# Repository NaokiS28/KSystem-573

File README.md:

# KSystem-573
 Schematics and pinout information for the Konami System 573
 
 **Please note a lot of this data is not 100% complete and might be incorrect in places.** Also this repository needs to be generally organised better.
 
## Schematics
 Schematics are in KiCad format and are preliminary. Currently known issues:
 * The PSX portion is not mapped out. This is the same as the regular PS1 CPU, GPU and SPU schematics with the exception of more work and GPU RAM.
 * The CPLD is mostly but not fully mapped out.
 * The security cart needs verifying and labeling correctly.
 * In general the schematics need tidying up.
 * The Konami 056789 ASIC needs a symbol creating. It's a 6x 16-Bit input and 1x 8-bit output latch really, probably has some 74 series dies on the inside.
 * IO boards are somewhat documented but in varying stages of completeness.

## PCB Layout
 The mother PCB is not laid out. The intention with this project was not to make a new repro motherboard but to define the schematics and wiring. The outline *should* be correct but it is not 100%. If you feel like creating a PCB layout, submit a PR!

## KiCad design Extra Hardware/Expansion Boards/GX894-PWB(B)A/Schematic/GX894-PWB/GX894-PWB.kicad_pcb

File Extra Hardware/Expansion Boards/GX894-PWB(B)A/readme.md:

# Konami 573 Digital Audio I/O Board (GX894)

This is the IO board that is mostly used with Bemani rhythm games. It uses a SPARTAN FPGA, Xilinx XC9536 CPLD and MAS3507D MP3 audio decoder IC withh a bunch of RAM, opto-isolators and trasceivers thrown in for good measure. The board is practically useless without an FPGA binary blob uploaded to it as nothing is accessible otherwise. This is uploaded by the game at the game's boot (and will show "Digital I/O init failure" if it can't.).

There's a dual RS232 port on the board but it seeminly went unused. There's also I2S audio output so it would be possible to capture the digital audio from the cab (and from the mainboard too) and convert to SPDIF or TOSLINK.

FWIW, the FPGA Blob that Konami uses is stored in 128k of SRAM and has a decryption engine built in that feeds data to the MAS chip, so you would need to encrypt any audio to be played back to use Konami's blob. Otherwise you could create a alternate blob that didn't require this and just use MP3 data stored in the 12 megabytes (!) of EDO RAM on the board.

There is Konami's multidrop networking bus and interface present on the board but more needs to be understood about this before it can be documented fully.

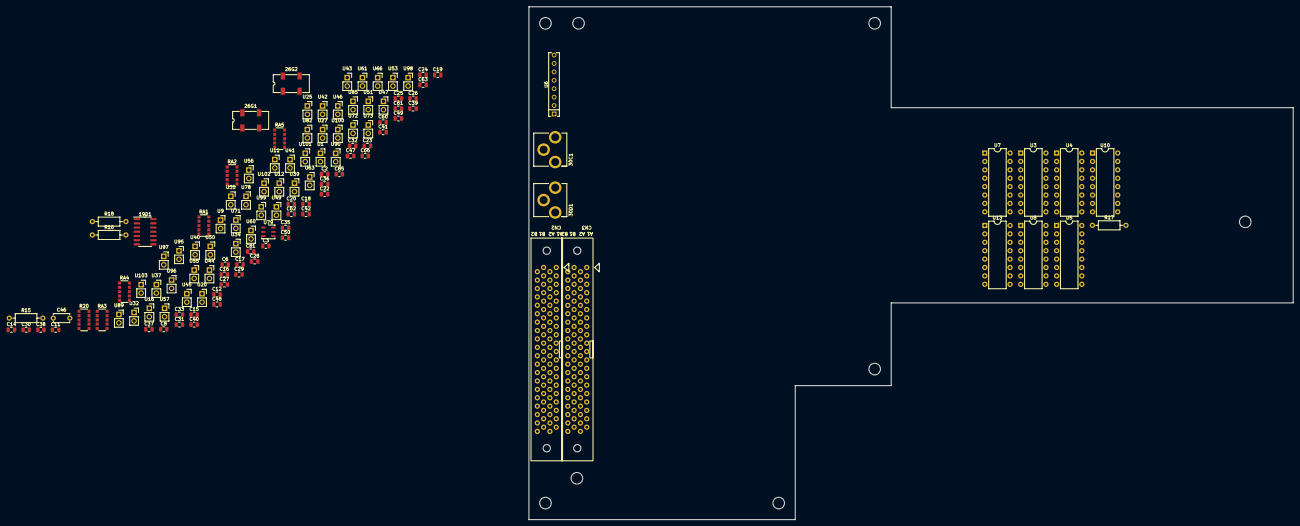
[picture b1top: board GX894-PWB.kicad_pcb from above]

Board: 2 copper layers, 231.0 x 155.0 mm, 128 parts (0 on the bottom side), 124 nets, no tracks yet.

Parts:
19D1: 74HC14; SOIC-14_3.9x8.7mm_P1.27mm
26G1: 29.45MHz; Oscillator_SMD_SeikoEpson_SG8002JC-4Pin_10.5x5.0mm
26G2: 19.6608 MHz; Oscillator_SMD_SeikoEpson_SG8002JC-4Pin_10.5x5.0mm
30C1, 30D1: JPJ1018; RCA_Mounting
C2, C3, C6, C8, C11, C12, C28, C29: 0.1µf; C_0805_2012Metric
C14, C15, C16, C17, C18, C19, C22, C23, C24, C25, C26, C27, C30, C31, C32, C33, C35, C36, C37, C38, C39, C40, C41, C42, C47, C48, C49, C50, C60, C61, C62, C63: 10nf; C_0805_2012Metric
C20, C66, C81, C85: 1uf; C_0805_2012Metric
C46: 0.01MC1K; C_Disc_D4.7mm_W2.5mm_P5.00mm
CN2, CN3: 573_EXP; JAE-TX15-80P
H1, H2, H3, H4, H5, H6, H7, H8: MountingHole; MountingHole_3.5mm
R15, R18: 100; R_Axial_DIN0207_L6.3mm_D2.5mm_P10.16mm_Horizontal
R16, R17: 5.6k; R_Axial_DIN0207_L6.3mm_D2.5mm_P10.16mm_Horizontal
R20: 470Ω; R_Array_Convex_5x1206
RA1: 4.7Ω; R_Array_Convex_5x1206
RA2, RA3, RA4: 470Ω; R_Array_Convex_5x1206
RA5: 2.2k; R_Array_Convex_5x1206
U1, U9, U11, U12, U16, U20, U25, U27, U32, U34, U35, U37, U39, U40, U41, U42, U43, U44, U45, U46, U47, U49, U50, U51, U53, U55, U56, U57, U60, U61, U63, U66, U71, U72, U73, U78, U82, U85, U89, U90, U95, U96, U97, U98, U99, U100, U101, U102, U103: ZBF253D; PinSocket_1x02_P2.54mm_Vertical
U3, U4, U5, U7, U8, U10, U13: PC847; DIP-16_W7.62mm
U6: HYC2485S; SIP-8_19x3mm_P2.54mm
U79: DS2401P; TSOC-6_3.76x3.94mm_P1.27mm

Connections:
573-A0: CN2.a24 (A0), CN3.a24 (A0)
573-A1: CN2.b24 (A1), CN3.b24 (A1)
573-A2: CN2.a23 (A2), CN3.a23 (A2)
573-A3: CN2.b23 (A3), CN3.b23 (A3)
573-A4: CN2.a22 (A4), CN3.a22 (A4)
573-A5: CN2.b22 (A5), CN3.b22 (A5)
573-A6: CN2.a21 (A6), CN3.a21 (A6)
573-A7: CN2.b21 (A7), CN3.b21 (A7)
573-A12: CN2.a20 (A12), CN3.a20 (A12)
573-A13: CN2.b20 (A13), CN3.b20 (A13)
573-A14: CN2.a19 (A14), CN3.a19 (A14)
573-A15: CN2.b19 (A15), CN3.b19 (A15)
573-A20: CN2.a18 (A20), CN3.a18 (A20)
573-A21: CN2.b18 (A21), CN3.b18 (A21)
573-A22: CN2.a17 (A22), CN3.a17 (A22)
573-A23: CN2.b17 (A23), CN3.b17 (A23)
573-D0: CN2.a32 (D0), CN3.a32 (D0)
573-D1: CN2.b32 (D1), CN3.b32 (D1)
573-D2: CN2.a31 (D2), CN3.a31 (D2)
573-D3: CN2.b31 (D3), CN3.b31 (D3)
573-D4: CN2.a30 (D4), CN3.a30 (D4)
573-D5: CN2.b30 (D5), CN3.b30 (D5)
573-D6: CN2.a29 (D6), CN3.a29 (D6)
573-D7: CN2.b29 (D7), CN3.b29 (D7)
573-D8: CN2.a28 (D8), CN3.a28 (D8)
573-D9: CN2.b28 (D9), CN3.b28 (D9)
573-D10: CN2.a27 (D10), CN3.a27 (D10)
573-D11: CN2.b27 (D11), CN3.b27 (D11)
573-D12: CN2.a26 (D12), CN3.a26 (D12)
573-D13: CN2.b26 (D13), CN3.b26 (D13)
573-D14: CN2.a25 (D14), CN3.a25 (D14)
573-D15: CN2.b25 (D15), CN3.b25 (D15)
+3V3: 26G1.1 (OE), 26G1.4 (Vcc), 26G2.1 (OE), 26G2.4 (Vcc), CN2.a36 (+3V3), CN2.a37 (+3V3), CN2.a38 (+3V3), CN2.a39 (+3V3), CN2.a40 (+3V3), CN2.b36 (+3V3), CN2.b37 (+3V3), CN2.b38 (+3V3), CN2.b39 (+3V3), CN2.b40 (+3V3), CN3.a36 (+3V3), CN3.a37 (+3V3), CN3.a38 (+3V3), CN3.a39 (+3V3), CN3.a40 (+3V3), CN3.b36 (+3V3), CN3.b37 (+3V3), CN3.b38 (+3V3), CN3.b39 (+3V3), CN3.b40 (+3V3)
+5V: 19D1.14 (VCC), C3.1, C20.1, C28.1, C66.1, C81.1, C85.1, CN2.a1 (+5V), CN2.a2 (+5V), CN2.a3 (+5V), CN2.a4 (+5V), CN2.a5 (+5V), CN2.b1 (+5V), CN2.b2 (+5V), CN2.b3 (+5V), CN2.b4 (+5V), CN2.b5 (+5V), CN3.a1 (+5V), CN3.a2 (+5V), CN3.a3 (+5V), CN3.a4 (+5V), CN3.a5 (+5V), CN3.b1 (+5V), CN3.b2 (+5V), CN3.b3 (+5V), CN3.b4 (+5V), CN3.b5 (+5V), R20.5 (common), R20.10 (common), RA1.5 (common), RA1.10 (common), RA2.5 (common), RA2.10 (common), RA3.5 (common), RA3.10 (common), RA4.5 (common), RA4.10 (common), U6.2 (VCC), U46.1
DREQ5: CN2.a14 (DREQ5), CN3.a14 (DREQ5)
DREQ5-2: CN2.b12 (DREQ5), CN3.b12 (DREQ5)
EXP-15: CN2.b15 (N/C), CN3.b15 (N/C)
GND: 19D1.1, 19D1.3, 19D1.7 (GND), 26G1.2 (GND), 26G2.2 (GND), C6.1, C11.1, C20.2, C30.2, C31.2, C32.2, C33.2, C46.2, C66.2, C81.2, C85.2, CN2.a8 (GND), CN2.a9 (GND), CN2.a11 (GND), CN2.a13 (GND), CN2.a33 (GND), CN2.a34 (GND), CN2.a35 (GND), CN2.b7 (GND), CN2.b9 (GND), CN2.b11 (GND), CN2.b13 (GND), CN2.b33 (GND), CN2.b34 (GND), CN2.b35 (GND), CN3.a8 (GND), CN3.a9 (GND), CN3.a11 (GND), CN3.a13 (GND), CN3.a33 (GND), CN3.a34 (GND), CN3.a35 (GND), CN3.b7 (GND), CN3.b9 (GND), CN3.b11 (GND), CN3.b13 (GND), CN3.b33 (GND), CN3.b34 (GND), CN3.b35 (GND), R16.1, RA5.5 (common), RA5.10 (common), U6.6 (GND), U12.1, U41.1, U47.1
IRQ10: CN2.a16 (IRQ10), CN3.a16 (IRQ10)
IRQ10-2: CN2.b16 (IRQ10), CN3.b16 (IRQ10)
unnamed: 19D1.5, C31.1
unnamed: 19D1.9, C33.1
unnamed: 19D1.11, C32.1
unnamed: 19D1.13, C30.1
unnamed: 30C1.1, 30D1.1, U6.5 (PH-A)
unnamed: 30C1.2 (Switch), R15.2
unnamed: 30C1.3 (Sheild), 30D1.3 (Sheild), C46.1, R15.1, R17.2, R18.2, U6.4 (PH-B)
unnamed: 30D1.2 (Switch), R18.1
unnamed: C14.1, U13.16, U25.1
unnamed: C14.2, C15.2, C16.2, C17.2, U13.9, U13.11, U13.13, U13.15, U60.1
unnamed: C15.1, U13.14, U102.1
unnamed: C16.1, U13.12, U101.1
unnamed: C17.1, U13.10, U100.1
unnamed: C18.1, U3.16, U99.1
unnamed: C18.2, C19.2, C38.2, C40.2, U3.9, U3.11, U3.13, U3.15, U50.1
unnamed: C19.1, U3.14, U98.1
unnamed: C22.1, U4.16, U95.1
unnamed: C22.2, C23.2, C24.2, C25.2, U4.9, U4.11, U4.13, U4.15, U35.1
unnamed: C23.1, U4.14, U44.1
unnamed: C24.1, U4.12, U90.1
unnamed: C25.1, U4.10, U82.1
unnamed: C26.1, U5.16, U89.1
unnamed: C26.2, C27.2, C35.2, C36.2, U5.9, U5.11, U5.13, U5.15, U45.1
unnamed: C27.1, U5.14, U71.1
unnamed: C35.1, U5.12, U34.1
unnamed: C36.1, U5.10, U40.1
unnamed: C37.1, U10.16, U73.1
unnamed: C37.2, C61.2, C62.2, C63.2, U10.9, U10.11, U10.13, U10.15, U72.1
unnamed: C38.1, U3.10, U96.1
unnamed: C39.1, U1.1, U8.10
unnamed: C39.2, C41.2, C42.2, C47.2, U8.9, U8.11, U8.13, U8.15, U63.1
unnamed: C40.1, U3.12, U97.1
unnamed: C41.1, U8.12, U9.1
unnamed: C42.1, U8.14, U16.1
unnamed: C47.1, U8.16, U27.1
unnamed: C48.1, U7.10, U39.1
unnamed: C48.2, C49.2, C50.2, C60.2, U7.9, U7.11, U7.13, U7.15, U37.1
unnamed: C49.1, U7.14, U53.1
unnamed: C50.1, U7.12, U43.1
unnamed: C60.1, U7.16, U56.1
unnamed: C61.1, U10.10, U103.1
unnamed: C62.1, U10.12, U51.1
unnamed: C63.1, U10.14, U61.1
unnamed: R16.2, R17.1
unnamed: R20.1 (R1), U7.1
unnamed: R20.2 (R2), U7.3
unnamed: R20.3 (R3), U7.5
unnamed: R20.4 (R4), U7.7
unnamed: R20.6 (R5), U8.7
unnamed: R20.7 (R6), U8.5
unnamed: R20.8 (R7), U8.3
unnamed: R20.9 (R8), U8.1
unnamed: RA1.1 (R1), RA5.1 (R1), U20.1
unnamed: RA1.4 (R4), RA5.4 (R4), U57.1
unnamed: RA1.3 (R3), RA5.3 (R3), U49.1
unnamed: RA1.2 (R2), RA5.2 (R2), U32.1
unnamed: RA2.1 (R1), U10.1
unnamed: RA2.2 (R2), U10.3
unnamed: RA2.3 (R3), U10.5
unnamed: RA2.4 (R4), U10.7
unnamed: RA2.6 (R5), U13.7
unnamed: RA2.7 (R6), U13.5
unnamed: RA2.8 (R7), U13.3
unnamed: RA2.9 (R8), U13.1
unnamed: RA3.1 (R1), U3.1
unnamed: RA3.2 (R2), U3.3
unnamed: RA3.3 (R3), U3.5
unnamed: RA3.4 (R4), U3.7
unnamed: RA3.6 (R5), U4.7
unnamed: RA3.7 (R6), U4.5
unnamed: RA3.8 (R7), U4.3
unnamed: RA3.9 (R8), U4.1
unnamed: RA4.1 (R1), U5.1
unnamed: RA4.2 (R2), U5.3
unnamed: RA4.3 (R3), U5.5
unnamed: RA4.4 (R4), U5.7
~EXP1-2: CN2.b14 (~EXP1), CN3.b14 (~EXP1)
~EXP1: CN2.a12 (~EXP1), CN3.a12 (~EXP1)
~EXP2: CN2.a15 (~EXP2), CN3.a15 (~EXP2)
~READ: CN2.a6 (~READ), CN3.a6 (~READ)
~RESET2: CN2.b10 (~RESET), CN3.b10 (~RESET)
~RESET: CN2.a10 (~RESET), CN3.a10 (~RESET)
~WR1: CN2.b6 (~WR1), CN3.b6 (~WR1)
~WR2: CN2.a7 (~WR2), CN3.a7 (~WR2)

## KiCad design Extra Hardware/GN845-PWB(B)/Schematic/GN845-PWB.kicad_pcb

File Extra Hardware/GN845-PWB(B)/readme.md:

# GN845-PWB(B) - Stage IO
This PCB is also known as the Stage IO board. It lives in either the top right or top left corner of the stage pads in Dance Dance Revolution/Dancing Stage and serves as a multiplexor and driver board for the stage neons. It's only used in DDR doubles cabs, DDR Solo does not use a multiplexor as it only uses two sensors per pad (vs DDR doubles' 4) and directly connects all sensors to the JAMMA connector. The JAMMA stick UDLR pins are connected to the Stage IO board, with U and R serving as inputs for the multiplexor data as well during boot and diagnostics.

Curiosly, the Stage IO is only ever populated for 4 arrows but an entire 5th section is on the PCB and routed out, so maybe DDR might have been a 5 panel game? This was before Pump-It-Up was released so it's interesting that perhaps the center panel might have originally been an input.

Power wise, the board receives a 12V input which is then connected to a 7805 to get local 5V regulated power.

## Function
The Stage IO is not exactly required in the sense that normal gameplay in DDR does not use nor care for the multiplexing of the Stage IO, it uses the direct JAMMA stick inputs for the arrows. That said the game *does* clock the Stage IO's serial bus during gameplay but it's not fully known why as grounding one of the pins (todo: which?) will enable the pad output anyway.

### Arrow Sections
Each arrow has it's own NPN darlington pair transistor, 74HC14 inverter and passives. The transistor is used for the neon drivers that light up the arrow panel. All sensors and the NPN transistor go through the logic inverter and then into the CPLD.

### CPLD
The CPLD has pullups on it's inputs after line filters (10nf LCL filters) that go through a resistor network. The inputs are also protected by a zener diode arrays to ground and to power. The outputs are protected by opto-isolators, the same PC817 chips that Konami used everywhere else.

The CPLD itself is not yet fully understood. It's known that all Stage IOs use a synchronous serial bus over 4 wires, two of which are inputs and driven by the System 573's opto-isolated outputs on the analogue or digital IO board. The other two lines share the U and R pins with the JAMMA connector. 

The serial protocol is **ludicrously slow**, it takes about 200ms(!) to transmit a complete message. The bus is full-duplex, like SPI, the 573 will receive data as it is being sent. The first packet is a mirror of what the 573 sends, the latter half has all of the sensor data (4x4 so 16 sensors) and the 573 can optionally disable individual sensors from use, probably to avoid a stuck input but this isn't used in gameplay.

The protocol will be documented here when it is more fully understood.

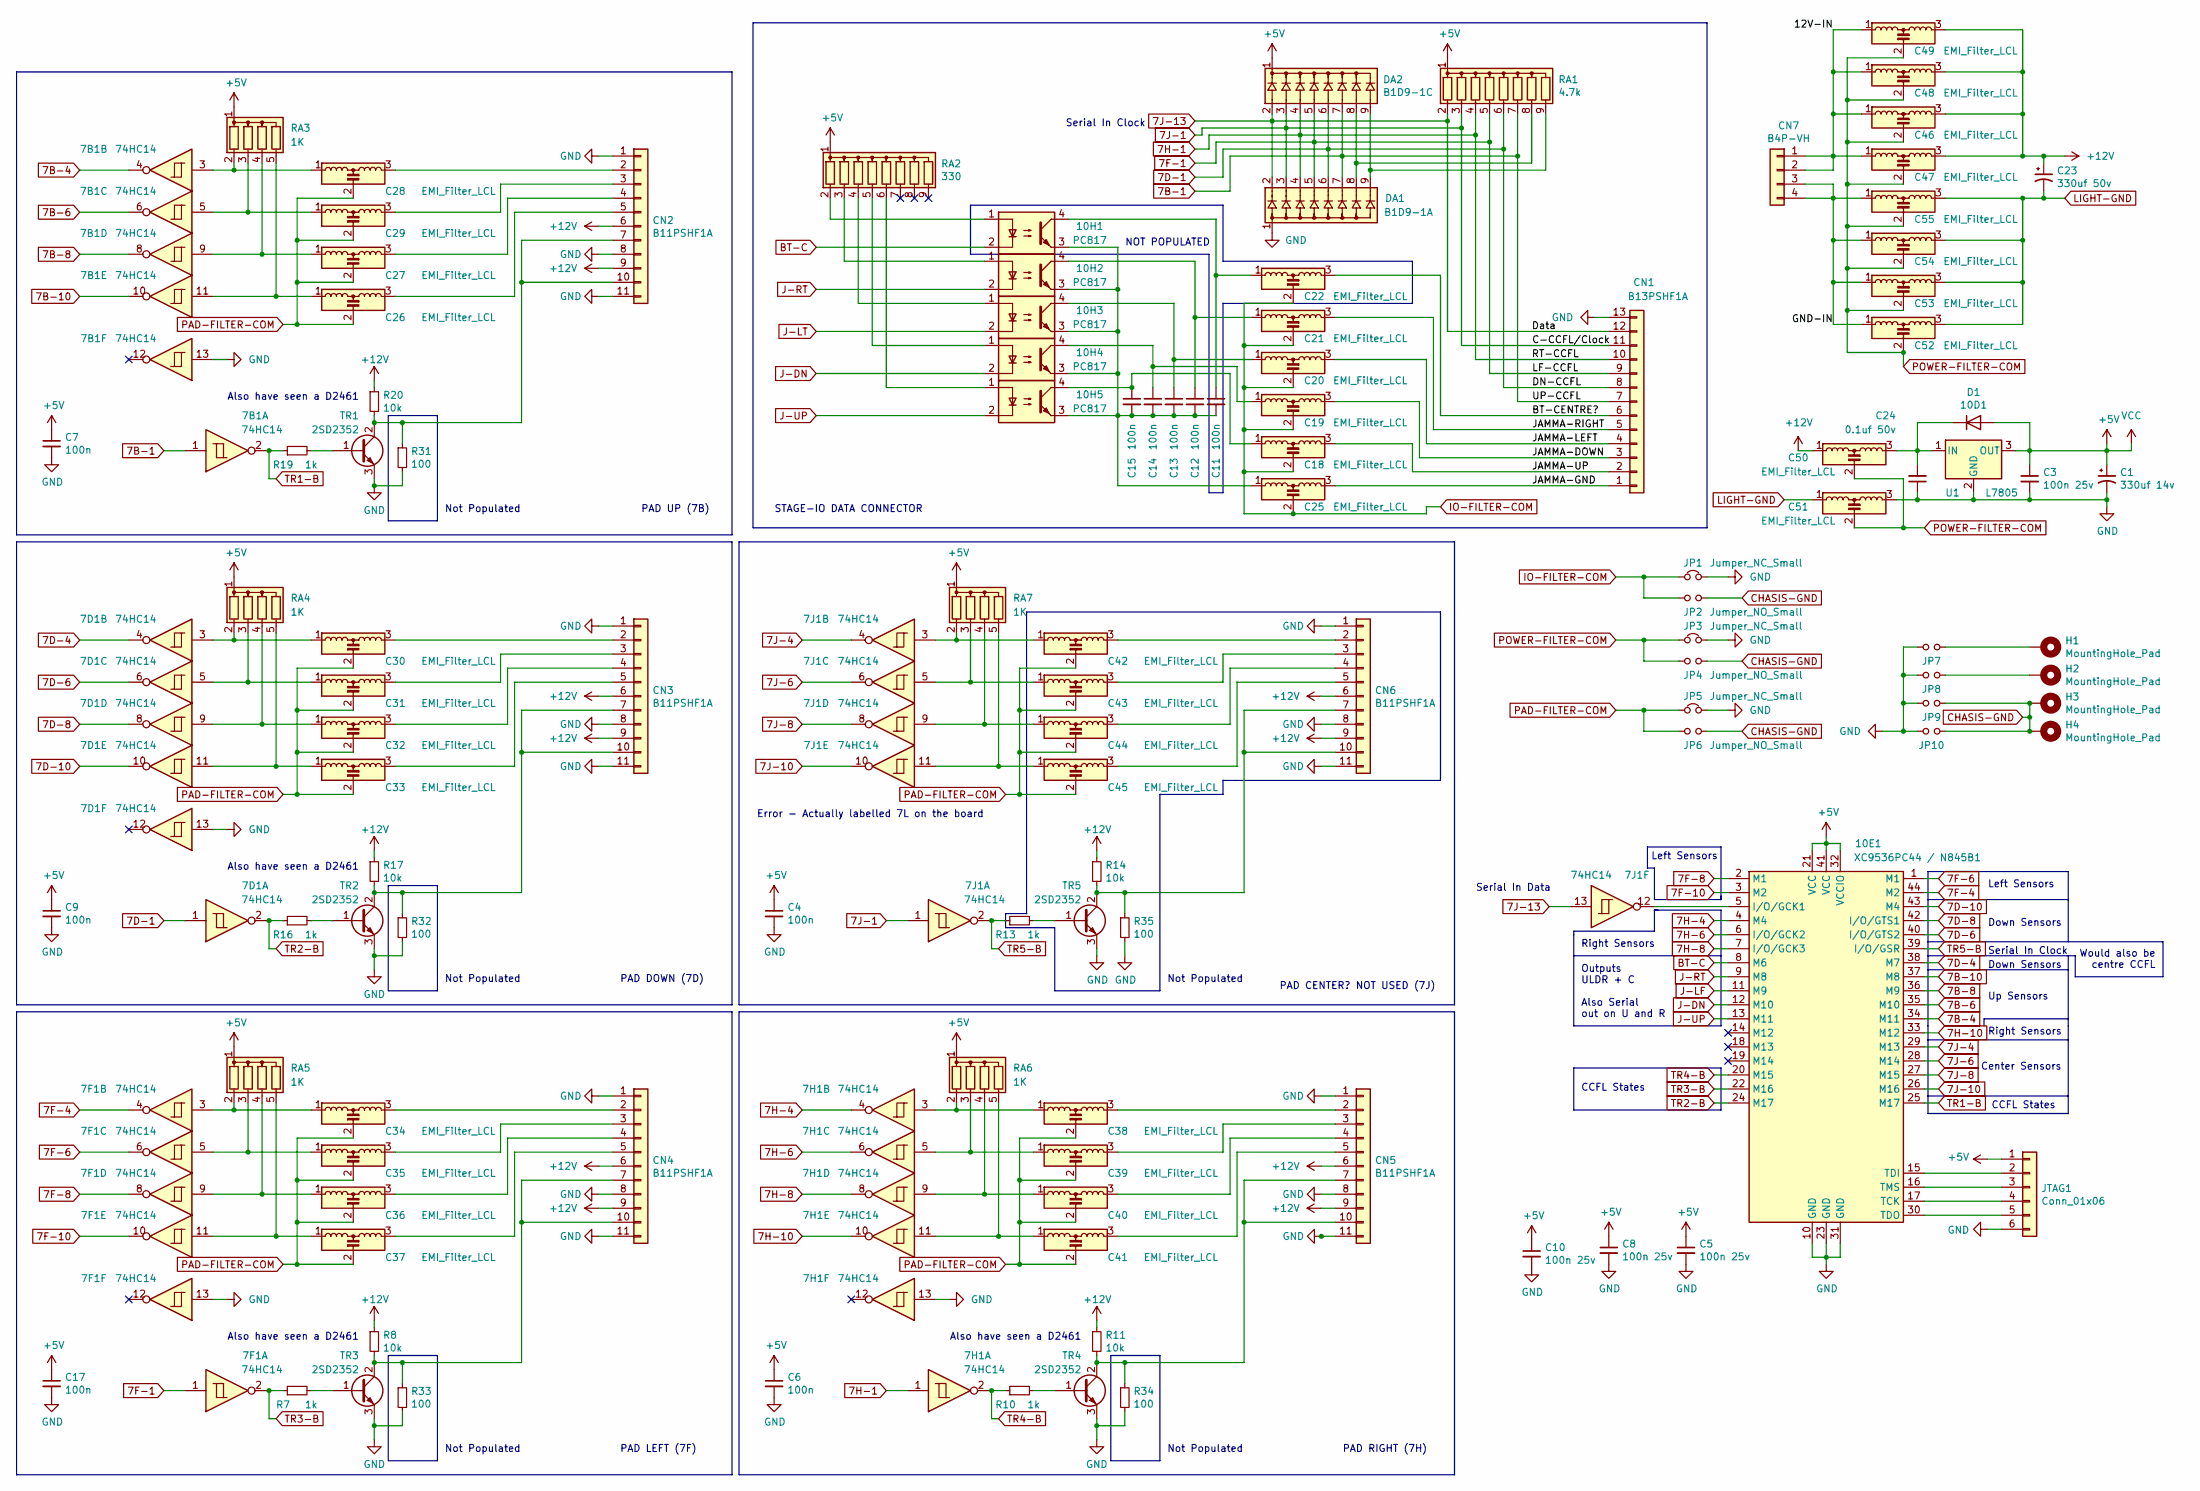
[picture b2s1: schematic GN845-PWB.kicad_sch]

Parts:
7B1, 7D1, 7F1, 7H1, 7J1: 74HC14; DIP-14_W7.62mm
10E1: XC9536PC44 / N845B1; PLCC-44
10H1, 10H2, 10H3, 10H4, 10H5: PC817; DIP-4_W7.62mm
C1: 330uf 14v; CP_Radial_D8.0mm_P3.50mm
C3, C5, C8, C10: 100n 25v; C_Axial_L3.8mm_D2.6mm_P10.00mm_Horizontal
C4, C6, C7, C9, C11, C12, C13, C14, C15, C17: 100n; C_Axial_L3.8mm_D2.6mm_P10.00mm_Horizontal
C18, C19, C20, C21, C22, C25, C26, C27, C28, C29, C30, C31, C32, C33, C34, C35, C36, C37, C38, C39, C40, C41, C42, C43, C44, C45, C46, C47, C48, C49, C50, C51, C52, C53, C54, C55: EMI_Filter_LCL; PinSocket_1x03_P2.54mm_Vertical
C23: 330uf 50v; CP_Radial_D8.0mm_P3.50mm
C24: 0.1uf 50v; C_Disc_D4.7mm_W2.5mm_P5.00mm
CN1: B13PSHF1A; JST_NH_B13P_SHD
CN2, CN3, CN4, CN5, CN6: B11PSHF1A; JST_NH_B11P_SHD
CN7: B4P-VH; JST_VH_B4P-VH-B_1x04_P3.96mm_Vertical
D1: 10D1; D_DO-41_SOD81_P10.16mm_Horizontal
DA1: B1D9-1A; SIP9_Housing
DA2: B1D9-1C; SIP9_Housing
H1, H2, H3, H4: MountingHole_Pad; MountingHole_3.2mm_M3_DIN965_Pad
JP1, JP3, JP5: Jumper_NC_Small; C_Rect_L7.0mm_W2.0mm_P5.00mm
JP2, JP4, JP6, JP7, JP8, JP9, JP10: Jumper_NO_Small; C_Rect_L7.0mm_W2.0mm_P5.00mm
JTAG1: Conn_01x06
R7, R10, R13, R16, R19: 1k; R_Axial_DIN0204_L3.6mm_D1.6mm_P5.08mm_Vertical
R8, R11, R14, R17, R20: 10k; R_Axial_DIN0204_L3.6mm_D1.6mm_P5.08mm_Vertical
R31, R32, R33, R34, R35: 100; R_Axial_DIN0204_L3.6mm_D1.6mm_P5.08mm_Vertical
RA1: 4.7k; R_Array_SIP9
RA2: 330; R_Array_SIP9
RA3, RA4, RA5, RA6, RA7: 1K; R_Array_SIP5
TR1, TR2, TR3, TR4, TR5: 2SD2352; TO-220-3_Horizontal_TabDown
U1: L7805; TO-220-3_Horizontal_TabDown

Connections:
7B-1: 7B1.1, CN1.7, DA1.7 (R6), DA2.7 (R6), RA1.7 (R6)
7B-4: 7B1.4, 10E1.34 (M11)
7B-6: 7B1.6, 10E1.35 (M10)
7B-8: 7B1.8, 10E1.36 (M9)
7B-10: 7B1.10, 10E1.37 (M8)
7D-1: 7D1.1, CN1.8, DA1.6 (R5), DA2.6 (R5), RA1.6 (R5)
7D-4: 7D1.4, 10E1.38 (M7)
7D-6: 7D1.6, 10E1.40 (I/O/GTS2)
7D-8: 7D1.8, 10E1.42 (I/O/GTS1)
7D-10: 7D1.10, 10E1.43 (M4)
7F-1: 7F1.1, CN1.9, DA1.5 (R4), DA2.5 (R4), RA1.5 (R4)
7F-4: 7F1.4, 10E1.44 (M2)
7F-6: 7F1.6, 10E1.1 (M1)
7F-8: 7F1.8, 10E1.2 (M1)
7F-10: 7F1.10, 10E1.3 (M2)
7H-1: 7H1.1, CN1.10, DA1.4 (R3), DA2.4 (R3), RA1.4 (R3)
7H-4: 7H1.4, 10E1.4 (M4)
7H-6: 7H1.6, 10E1.6 (I/O/GCK2)
7H-8: 7H1.8, 10E1.7 (I/O/GCK3)
7H-10: 7H1.10, 10E1.33 (M12)
7J-1: 7J1.1, CN1.11, DA1.3 (R2), DA2.3 (R2), RA1.3 (R2)
7J-4: 7J1.4, 10E1.29 (M13)
7J-6: 7J1.6, 10E1.28 (M14)
7J-8: 7J1.8, 10E1.27 (M15)
7J-10: 7J1.10, 10E1.26 (M16)
7J-13: 7J1.13, CN1.12, DA1.2 (R1), DA2.2 (R1), RA1.2 (R1)
+5V: 10E1.21 (VCC), 10E1.32 (VCCIO), 10E1.41 (VCC), C1.1, C3.1, C4.1, C5.1, C6.1, C7.1, C8.1, C9.1, C10.1, C17.1, D1.2 (A), DA2.1 (common), JTAG1.1, RA1.1 (common), RA2.1 (common), RA3.1 (common), RA4.1 (common), RA5.1 (common), RA6.1 (common), RA7.1 (common), U1.3 (OUT)
+12V: C23.1, C46.3, C47.3, C48.3, C49.3, C50.1, CN2.6, CN2.9, CN3.6, CN3.9, CN4.6, CN4.9, CN5.6, CN5.9, CN6.6, CN6.9, R8.1, R11.1, R14.1, R17.1, R20.1
/12V-IN: C46.1, C47.1, C48.1, C49.1, CN7.1, CN7.2
/BT-CENTRE?: C22.3, CN1.6
/GND-IN: C52.1, C53.1, C54.1, C55.1, CN7.3, CN7.4
/JAMMA-DOWN: C19.3, CN1.3
/JAMMA-GND: C25.3, CN1.1
/JAMMA-LEFT: C20.3, CN1.4
/JAMMA-RIGHT: C21.3, CN1.5
/JAMMA-UP: C18.3, CN1.2
BT-C: 10E1.8 (M6), 10H1.2
CHASIS-GND: H3.1, H4.1, JP2.2, JP4.2, JP6.2, JP9.2, JP10.2
GND: 7B1.13, 7D1.13, 7F1.13, 7H1.13, 10E1.10 (GND), 10E1.23 (GND), 10E1.31 (GND), C1.2, C3.2, C4.2, C5.2, C6.2, C7.2, C8.2, C9.2, C10.2, C17.2, C24.1, C51.3, CN1.13, CN2.1, CN2.8, CN2.11, CN3.1, CN3.8, CN3.11, CN4.1, CN4.8, CN4.11, CN5.1, CN5.8, CN5.11, CN6.1, CN6.8, CN6.11, DA1.1 (common), JP1.2, JP3.2, JP5.2, JP7.1, JP8.1, JP9.1, JP10.1, JTAG1.6, R31.2, R32.2, R33.2, R34.2, R35.2, TR1.3 (E), TR2.3 (E), TR3.3 (E), TR4.3 (E), TR5.3 (E), U1.2 (GND)
IO-FILTER-COM: C18.2, C19.2, C20.2, C21.2, C22.2, C25.2, JP1.1, JP2.1
J-DN: 10E1.12 (M10), 10H4.2
J-LF: 10E1.11 (M9)
J-LT: 10H3.2
J-RT: 10E1.9 (M8), 10H2.2
J-UP: 10E1.13 (M11), 10H5.2
LIGHT-GND: C23.2, C51.1, C52.3, C53.3, C54.3, C55.3
unnamed: 7B1.3, C28.1, RA3.2 (R1)
unnamed: 7B1.5, C29.1, RA3.3 (R2)
unnamed: 7B1.9, C27.1, RA3.4 (R3)
unnamed: 7B1.11, C26.1, RA3.5 (R4)
unnamed: 7D1.3, C30.1, RA4.2 (R1)
unnamed: 7D1.5, C31.1, RA4.3 (R2)
unnamed: 7D1.9, C32.1, RA4.4 (R3)
unnamed: 7D1.11, C33.1, RA4.5 (R4)
unnamed: 7F1.3, C34.1, RA5.2 (R1)
unnamed: 7F1.5, C35.1, RA5.3 (R2)
unnamed: 7F1.9, C36.1, RA5.4 (R3)
unnamed: 7F1.11, C37.1, RA5.5 (R4)
unnamed: 7H1.3, C38.1, RA6.2 (R1)
unnamed: 7H1.5, C39.1, RA6.3 (R2)
unnamed: 7H1.9, C40.1, RA6.4 (R3)
unnamed: 7H1.11, C41.1, RA6.5 (R4)
unnamed: 7J1.3, C42.1, RA7.2 (R1)
unnamed: 7J1.5, C43.1, RA7.3 (R2)
unnamed: 7J1.9, C44.1, RA7.4 (R3)
unnamed: 7J1.11, C45.1, RA7.5 (R4)
unnamed: 7J1.12, 10E1.5 (I/O/GCK1)
unnamed: 10E1.15 (TDI), JTAG1.2
unnamed: 10E1.16 (TMS), JTAG1.3
unnamed: 10E1.17 (TCK), JTAG1.4
unnamed: 10E1.30 (TDO), JTAG1.5
unnamed: 10H1.1, RA2.2 (R1)
unnamed: 10H1.3, 10H2.3, 10H3.3, 10H4.3, 10H5.3, C11.2, C12.2, C13.2, C14.2, C15.2, C25.1
unnamed: 10H1.4, C11.1, C22.1
unnamed: 10H2.1, RA2.3 (R2)
unnamed: 10H2.4, C12.1, C21.1
unnamed: 10H3.1, RA2.4 (R3)
unnamed: 10H3.4, C13.1, C20.1
unnamed: 10H4.1, RA2.5 (R4)
unnamed: 10H4.4, C14.1, C19.1
unnamed: 10H5.1, RA2.6 (R5)
unnamed: 10H5.4, C15.1, C18.1
unnamed: C24.2, C50.3, D1.1 (K), U1.1 (IN)
unnamed: C26.3, CN2.5
unnamed: C27.3, CN2.4
unnamed: C28.3, CN2.2
unnamed: C29.3, CN2.3
unnamed: C30.3, CN3.2
unnamed: C31.3, CN3.3
unnamed: C32.3, CN3.4
unnamed: C33.3, CN3.5
unnamed: C34.3, CN4.2
unnamed: C35.3, CN4.3
unnamed: C36.3, CN4.4
unnamed: C37.3, CN4.5
unnamed: C38.3, CN5.2
unnamed: C39.3, CN5.3
unnamed: C40.3, CN5.4
unnamed: C41.3, CN5.5
unnamed: C42.3, CN6.2
unnamed: C43.3, CN6.3
unnamed: C44.3, CN6.4
unnamed: C45.3, CN6.5
unnamed: CN2.7, CN2.10, R20.2, R31.1, TR1.2 (C)
unnamed: CN3.7, CN3.10, R17.2, R32.1, TR2.2 (C)
unnamed: CN4.7, CN4.10, R8.2, R33.1, TR3.2 (C)
unnamed: CN5.7, CN5.10, R11.2, R34.1, TR4.2 (C)
unnamed: CN6.7, CN6.10, R14.2, R35.1, TR5.2 (C)
unnamed: DA1.8 (R7), DA2.8 (R7), RA1.8 (R7)
unnamed: DA1.9 (R8), DA2.9 (R8), RA1.9 (R8)
unnamed: H1.1, JP7.2
unnamed: H2.1, JP8.2
unnamed: R7.2, TR3.1 (B)
unnamed: R10.2, TR4.1 (B)
unnamed: R13.2, TR5.1 (B)
unnamed: R16.2, TR2.1 (B)
unnamed: R19.2, TR1.1 (B)
PAD-FILTER-COM: C26.2, C27.2, C28.2, C29.2, C30.2, C31.2, C32.2, C33.2, C34.2, C35.2, C36.2, C37.2, C38.2, C39.2, C40.2, C41.2, C42.2, C43.2, C44.2, C45.2, JP5.1, JP6.1
POWER-FILTER-COM: C46.2, C47.2, C48.2, C49.2, C50.2, C51.2, C52.2, C53.2, C54.2, C55.2, JP3.1, JP4.1
TR1-B: 7B1.2, 10E1.25 (M17), R19.1
TR2-B: 7D1.2, 10E1.24 (M17), R16.1
TR3-B: 7F1.2, 10E1.22 (M16), R7.1
TR4-B: 7H1.2, 10E1.20 (M15), R10.1
TR5-B: 7J1.2, 10E1.39 (I/O/GSR), R13.1

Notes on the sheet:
Up Sensors
Right Sensors
Center Sensors
STAGE-IO DATA CONNECTOR
Not Populated
Error - Actually labelled 7L on the board
Serial In Clock
Down Sensors
CCFL States
PAD DOWN (7D)
Also have seen a D2461
Left Sensors
PAD CENTER? NOT USED (7J)
NOT POPULATED
PAD LEFT (7F)
Outputs ULDR + C Also Serial out on U and R
PAD UP (7B)
Would also be centre CCFL
PAD RIGHT (7H)
Serial In Data

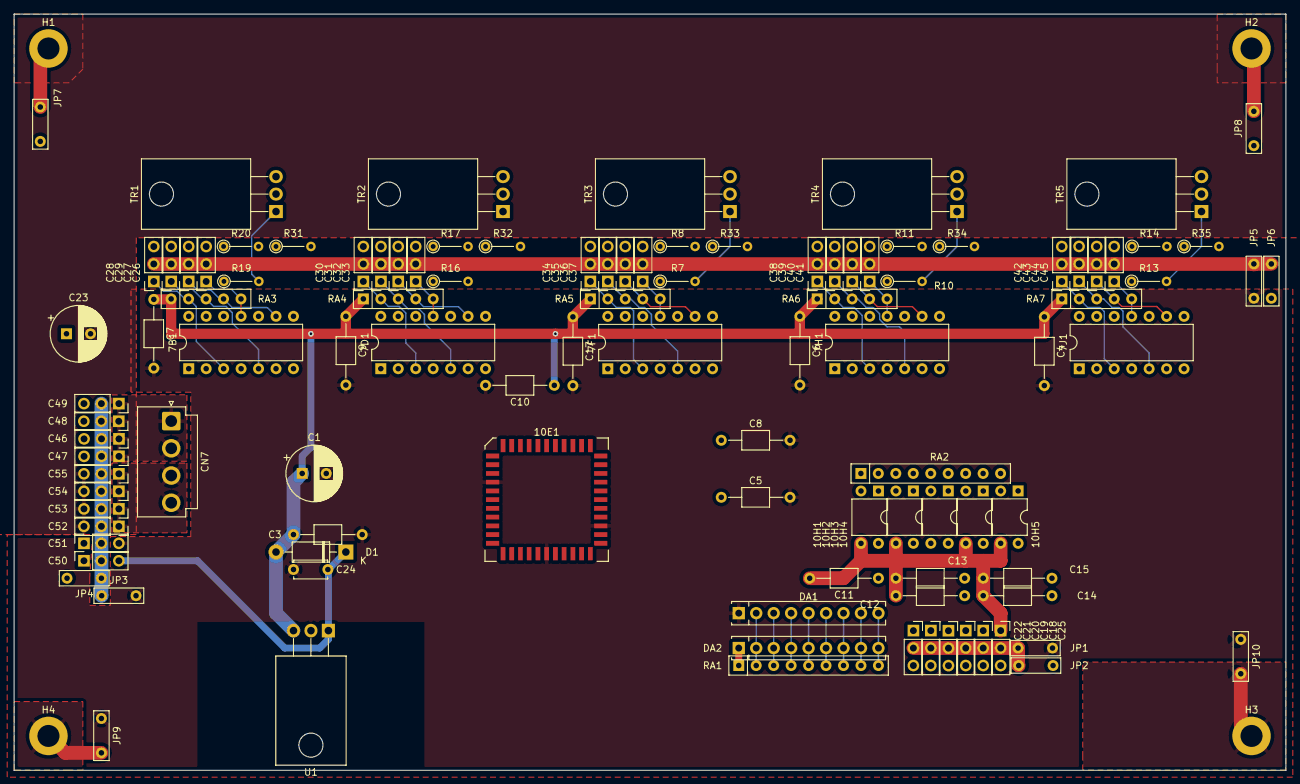
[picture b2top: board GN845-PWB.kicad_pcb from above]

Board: 2 copper layers, 185.0 x 110.0 mm, 110 parts (0 on the bottom side), 92 nets.

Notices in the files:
Extra Hardware/Expansion Boards/GX700-PWB(F)/Schematic/GX700-PWB.kicad_pcb:
©KOMANI ALL RIGHTS RESERVED.
